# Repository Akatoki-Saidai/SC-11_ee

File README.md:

# SC-11_ee

## Arduino Pin使用番号

## 各種センサ動作確認結果

<table>
    <tr>
        <td width="20%" rowspan="3">三軸加速度</td>
        <td>analogRead()で電圧を読んでシリアルモニタに表示することはできた</td>
    </tr>
    <tr>
        <td>ふってみてデータを見た感じ変化はしているのでちゃんと取れてる？</td>
    </tr>
    <tr>
        <td>生データを表示しているのでわかりにくいので，[m/s^2]表記への変換が必要</td>
    </tr>
    <tr>
        <td rowspan="3">3軸角速度</td>
        <td>https://n.mtng.org/ele/arduino/tutorial017.html</td>
    </tr>
    <tr>
        <td>レジスタ等の変更が必要らしい</td>
    </tr>
    <tr>
        <td>単位は [°/sec]</td>
    </tr>
    <tr>
        <td rowspan="4">BME280</td>
        <td>高度がマイナスになるのは海面気圧が問題？</td>
    </tr>
    <tr>
        <td>SC-10で購入したSwitchScience製のBME280で動作確認</td>
    </tr>
    <tr>
        <td>高度は↓のサイトを参照</td>
    </tr>
    <tr>
        <td>https://keisan.casio.jp/exec/system/1203469826</td>
    </tr>
        <tr>
        <td rowspan="3">DRV8835</td>
        <td>モーターを動かす時間がなかったのでLEDでテスト</td>
    </tr>
    <tr>
        <td>「加速」「減速」以外はLEDでは正常に動作</td>
    </tr>
    <tr>
        <td>「加速」は「減速」は確認できなかった（エラーは出てない）</td>
    </tr>
</table>

## モード定義

この セクションでは各モードの概要を説明する．

#### 待機モード (Mode-N)

- このモードでは基本的には「何もしない」というモードですが，以下のセンサーのキャリブレーション・実行準備を実施します．
  
  - 加速度センサー
  - 角速度センサー
  - 地磁気センサー
  - ブラシレスモーター

- 以下の定義を全て満たした場合に `Mode-A` に移行するものとする．
  
  1. Arduino Nanoが起動してから `30 sec` 以上経過している
  
  2. CanSatの高度が `TBD m` 以上である
  
  3. CanSatが落下を検知
     
     :pencil2: 落下を検知とは：未定義

#### 機体安定モード (Mode-A)

- このモードでは機体を安定させることに特化した（またはそれのみを実施する）モードである．
  - 機体がある程度安定したら，`Mode-B`に移行し，機体を的確に制御する．

#### 機体制御モード (Mode-B)

- このモードでは機体を制御させることに特化した（またはそれのみを実施する）モードである．特に，ゴールへの制御を実行する．
  - 機体制御が困難になった場合は，`Mode-A`に移行する．
  - ゴールから`TBD`m以内に入ったら`Mode-F`

#### 最終着地モード (Mode-F)

- このモードではゴールとの距離を維持したまま下降することのみに特化したモード

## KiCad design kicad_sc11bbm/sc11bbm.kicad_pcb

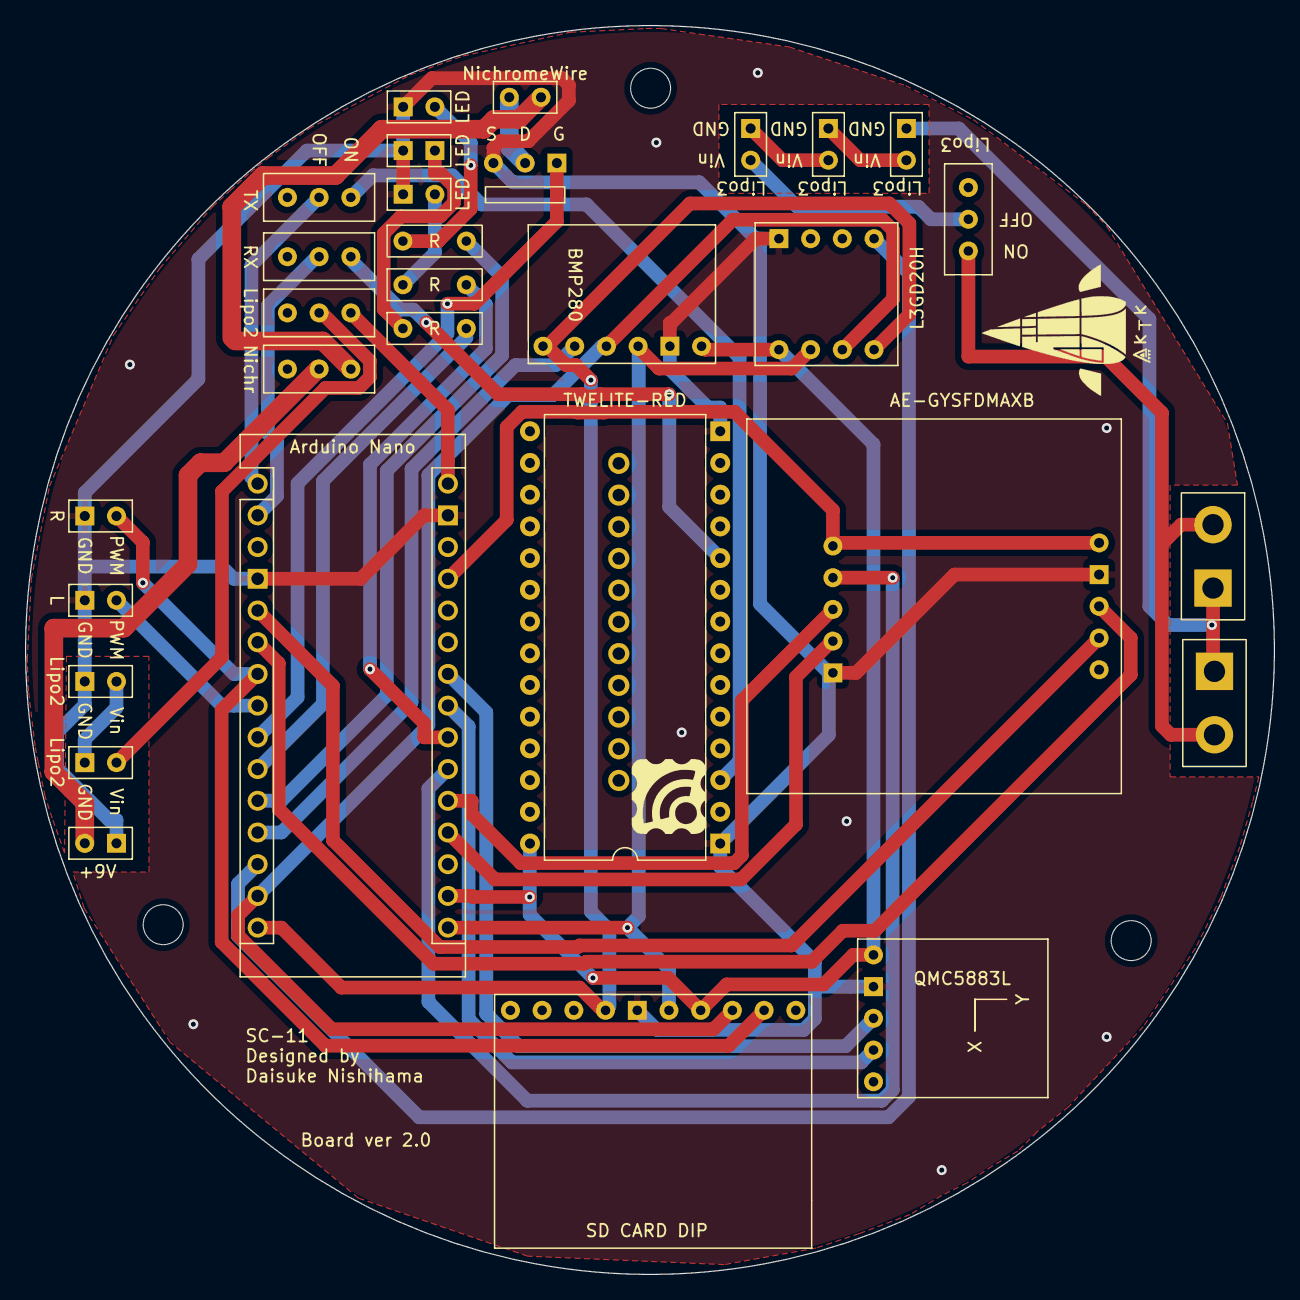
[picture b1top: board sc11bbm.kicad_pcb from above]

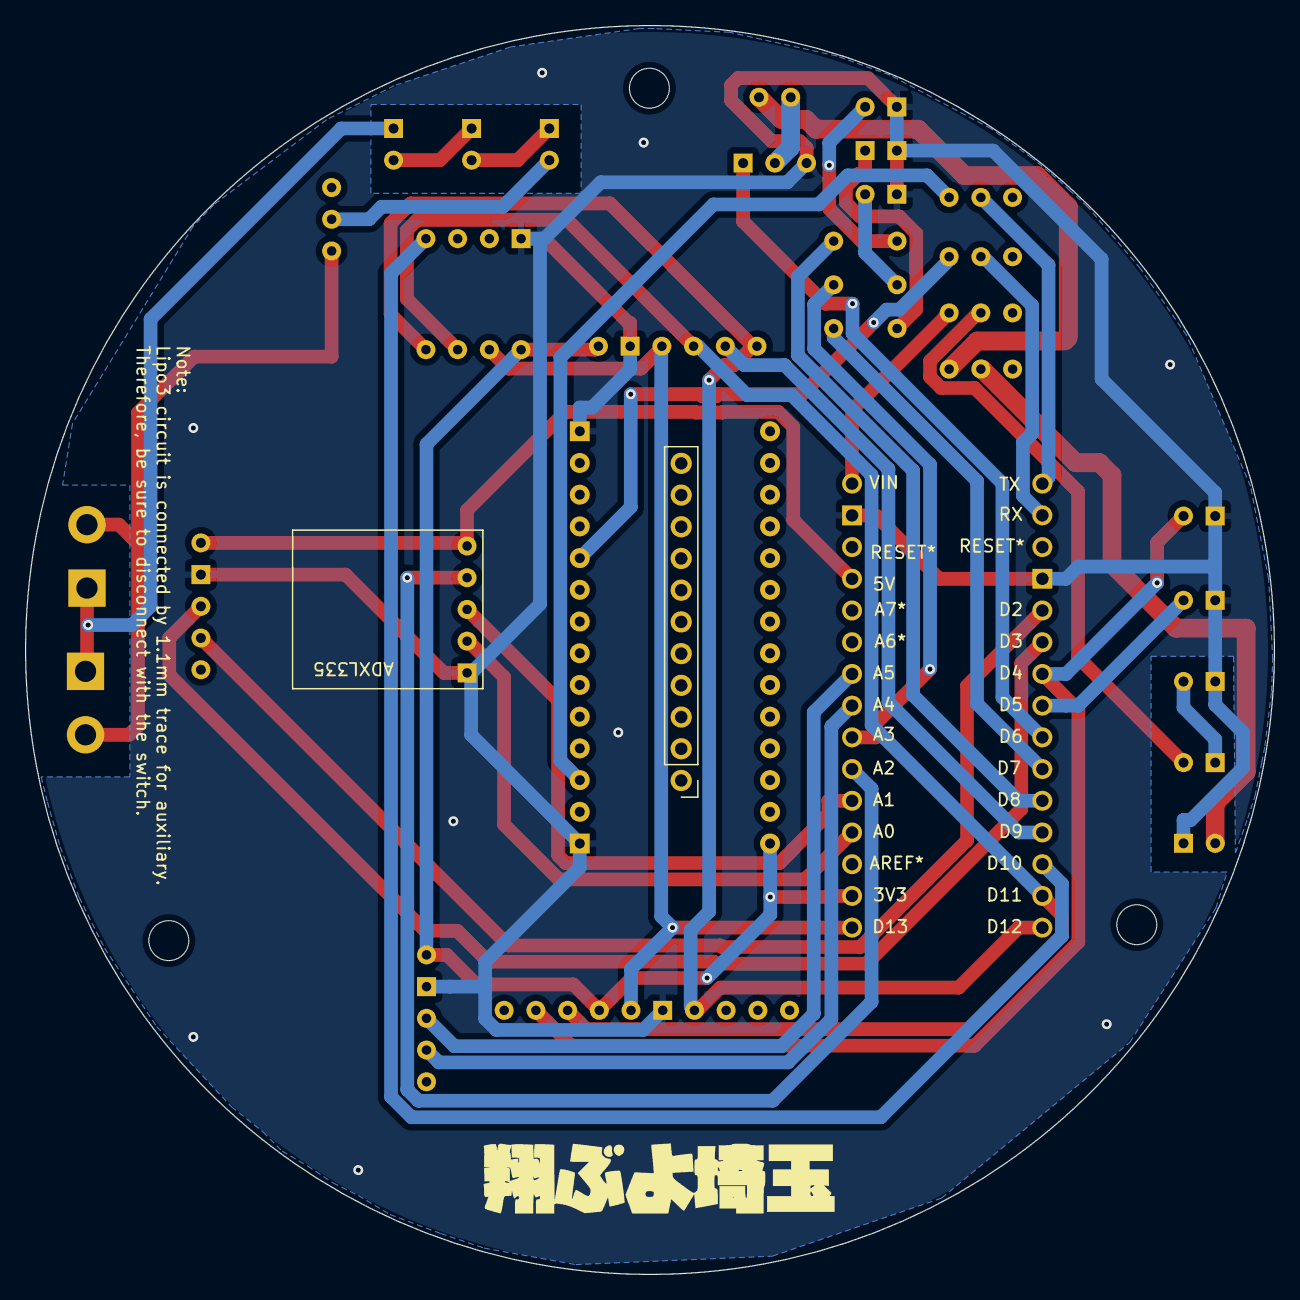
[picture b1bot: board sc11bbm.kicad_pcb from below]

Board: 2 copper layers, 100.0 x 100.0 mm, 36 parts (2 on the bottom side), 36 nets.

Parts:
A1: Arduino_Nano_v3.x; Arduino_Nano
BT1, BT4: Lipo2
BT2: +9V; power_9v
BT3, BT5, BT6: Lipo3
C2: bighole
CI1: bighole
D1, D2, D3: LED
G1: LOGO; sc11logo2
G2: LOGO; akatoki_logo12
M1, M2, M3: MountingHole_3.2mm_M3_ISO14580
Q1: 2SK4017
R1, R2, R3: R; Resistor
RV1: NichromeWire
SW1, SW2, SW3, SW4, SW5: SW_SPST; swicth
U1: ESC_R
U2: ESC_L
U3: L3GD20H
U4: QMC5883L
U5: BMP280
U6: MW-R-DP-W; DIP-28_W15.24mm
U7: AE-GYSFDMAXB
U8: ADXL335
U9: SD_CARD_DIP

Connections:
3V3: A1.17 (3V3), U3.1 (+V), U4.1 (VCC), U5.1 (VCC), U6.28 (VCC), U9.4 (VDD)
5V: A1.27 (+5V), U7.1 (5V), U8.1 (VCC)
A0: A1.19 (A0), U8.4 (Z_out)
A1: A1.20 (A1), U8.3 (Y_out)
A2: A1.21 (A2), U8.2 (X_out)
A3: A1.22 (A3), R3.2
A4: A1.23 (A4), U4.4 (SDA)
A5: A1.24 (A5), U4.3 (SCL)
D2: A1.5 (D2), U7.4 (TXD)
D3: A1.6 (D3), U7.3 (RXD)
D4: A1.7 (D4), U1.1 (PWM), U9.2 (CD/DAT3)
D5: A1.8 (D5), U2.1 (PWM)
D6: A1.9 (D6), Q1.1 (G)
D7: A1.10 (D7), R1.2
D8: A1.11 (D8), R2.2
D9: A1.12 (D9), U5.5 (CSB)
D10: A1.13 (D10), U3.5 (CS)
D11: A1.14 (D11), U3.3 (SDA), U5.4 (SDA), U9.3 (CMD)
D12: A1.15 (D12), U3.4 (SA0), U5.6 (SDO), U9.7 (DAT0)
D13: A1.16 (D13), U3.2 (SCL), U5.3 (SCL), U9.5 (CLK)
GND: A1.4 (GND), A1.29 (GND), BT1.2 (-), BT2.2 (-), D1.1 (K), D2.1 (K), D3.1 (K), Q1.3 (S), U1.3 (GND), U2.3 (GND), U3.8 (GND), U4.2 (GND), U5.2 (GND), U6.1 (GND), U6.14 (GND), U7.2 (GND), U8.5 (GND), U9.6 (VSS)
Lipo2: A1.30 (VIN), SW1.1 (A)
Lipo3: C2.1, CI1.1, SW5.1 (A)
unnamed: A1.1 (D1/TX), SW3.2 (B)
unnamed: A1.2 (D0/RX), SW2.2 (B)
unnamed: BT1.1 (+), BT4.2 (-)
unnamed: BT2.1 (+), SW4.2 (B)
unnamed: BT6.4, SW5.2 (B)
unnamed: D1.2 (A), R1.1
unnamed: D2.2 (A), R2.1
unnamed: D3.2 (A), R3.1
unnamed: Q1.2 (D), RV1.1
unnamed: RV1.2, SW4.1 (A)
unnamed: BT4.1 (+), SW1.2 (B)
RX: SW2.1 (A), U6.10 (DIO6/TX)
TX: SW3.1 (A), U6.3 (DIO7/RX)

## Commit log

2022-06-01 Made Kicad BBM folders
    KiCad共同開発用プロジェクトフォルダをアップロードしました．
2022-06-01 Just Creat README
    何も書いてません．とりあえず作っただけです．
2022-06-10 Create testcode_qyf0237.ino
    加速度センサー用のテストコードですが，ハードが悪いのか（Arduino Nanoが悪いのか），ソフトが悪いのか（コードが悪いのか）調べられていません．
2022-06-17 updated by Tsuchihashi
2022-06-18 Rename "sc11bbm" "kicad_sc11bbm"
2022-06-18 test
2022-06-18 Update gyro.ino
    delayを1000から10に変更した
2022-06-24 QMC5883L.test
2022-06-24 delete
2022-06-24 2nd commit
2022-06-26 Update motor.ino
    ブラシレスモーター用のコードに変更
2022-06-30 1st commit
2022-07-06 Add some files related to Brushless motor
2022-07-10 Reference settings are not yet
2022-07-10 Subtle changes to the schematic
2022-07-11 Circuit diagram completed
2022-07-11 Order completed for Board ver1.0
2022-07-11 Made step file
2022-07-13 delete_backup
2022-07-13 Revert "Merge branch 'main' into kicad"
    This reverts commit 1ffaabe5a03e4900a6120109884412335f5f846d, reversing
    changes made to 30488b6ef0ed4470b394fc2428748494f3e7c96e.
2022-07-18 Update bbm_code.ino
    動作確認はまだできてないです
    申しわけない
    動くと信じて...
    to be continued...
2022-08-03 For EM board2
2022-08-28 Update 回路PDF
